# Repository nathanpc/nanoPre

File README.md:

# nanoPre

A simple, battery powered, HiFi preamp.

## Schematics

This is the pre-amplifier. As you can see it's extremely simple and it's designed to be able to fit in any enclosure (but it was designed to fit inside [this one](http://www.aliexpress.com/item/Aluminum-Project-Box-Enclousure-Case-Electronic-DIY-Power-amplifier-aluminum-shell-PCB-shell-power-instrument-shell/1799375798.html)).

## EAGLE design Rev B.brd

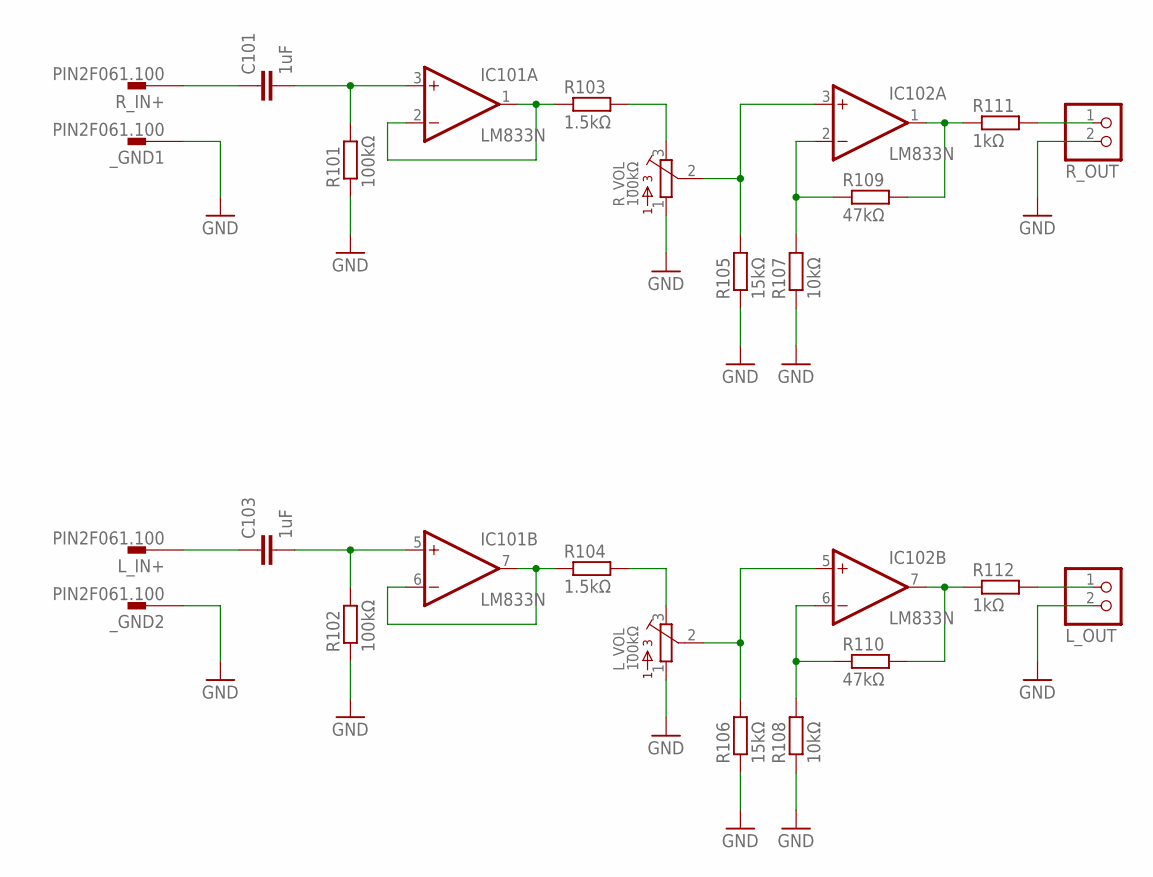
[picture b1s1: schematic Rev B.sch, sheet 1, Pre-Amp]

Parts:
C101, C103: 1uF; C150-072X183
IC101, IC102: LM833N; DIL08
L_IN+: PIN2F061.100; F061.100
L_OUT: JST_2PIN-THM; JST-PH-2-THM
L_VOL: 100kΩ; 3362U
R101, R102: 100kΩ; 0207/10
R103, R104: 1.5kΩ; 0207/10
R105, R106: 15kΩ; 0207/10
R107, R108: 10kΩ; 0207/10
R109, R110: 47kΩ; 0207/10
R111, R112: 1kΩ; 0207/10
R_IN+: PIN2F061.100; F061.100
R_OUT: JST_2PIN-THM; JST-PH-2-THM
R_VOL: 100kΩ; 3362U
_GND1, _GND2: PIN2F061.100; F061.100

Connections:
GND: L_OUT.2 (1), L_VOL.1, R101.1, R102.1, R105.1, R106.1, R107.1, R108.1, R_OUT.2 (1), R_VOL.1, _GND1.A1, _GND1.A2, _GND2.A1, _GND2.A2; also elsewhere on the board
unnamed: L_OUT.1 (2), R112.2
unnamed: R111.2, R_OUT.1 (2)
unnamed: C101.2, IC101.3 (+IN), R101.2
unnamed: C103.2, IC101.5 (+IN), R102.2
unnamed: C101.1, R_IN+.A1, R_IN+.A2
unnamed: C103.1, L_IN+.A1, L_IN+.A2
unnamed: IC101.1 (OUT), IC101.2 (-IN), R103.1
unnamed: IC102.3 (+IN), R105.2, R_VOL.2
unnamed: R103.2, R_VOL.3
unnamed: IC102.2 (-IN), R107.2, R109.1
unnamed: IC102.1 (OUT), R109.2, R111.1
unnamed: IC101.6 (-IN), IC101.7 (OUT), R104.1
unnamed: IC102.5 (+IN), L_VOL.2, R106.2
unnamed: L_VOL.3, R104.2
unnamed: IC102.6 (-IN), R108.2, R110.1
unnamed: IC102.7 (OUT), R110.2, R112.1

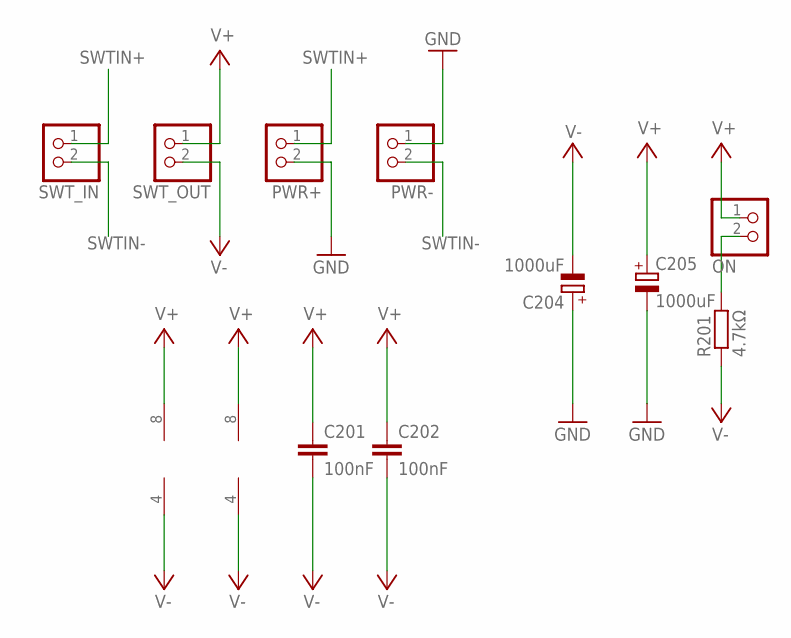
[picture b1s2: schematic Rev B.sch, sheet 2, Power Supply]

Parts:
C201, C202: 100nF; C025-025X050
C204, C205: 1000uF; E5-10,5
IC101, IC102: LM833N; DIL08
ON: JST_2PIN-THM; JST-PH-2-THM
PWR+: JST_2PIN-THM; JST-PH-2-THM
PWR-: JST_2PIN-THM; JST-PH-2-THM
R201: 4.7kΩ; 0207/10
SWT_IN: JST_2PIN-THM; JST-PH-2-THM
SWT_OUT: JST_2PIN-THM; JST-PH-2-THM

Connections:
GND: C204.+, C205.-, PWR+.2 (1), PWR-.1 (2); also elsewhere on the board
unnamed: ON.2 (1), R201.2
SWTIN+: PWR+.1 (2), SWT_IN.1 (2)
SWTIN-: PWR-.2 (1), SWT_IN.2 (1)
V+: C201.1, C202.1, C205.+, IC101.8 (V+), IC102.8 (V+), ON.1 (2), SWT_OUT.1 (2)
V-: C201.2, C202.2, C204.-, IC101.4 (V-), IC102.4 (V-), R201.1, SWT_OUT.2 (1)

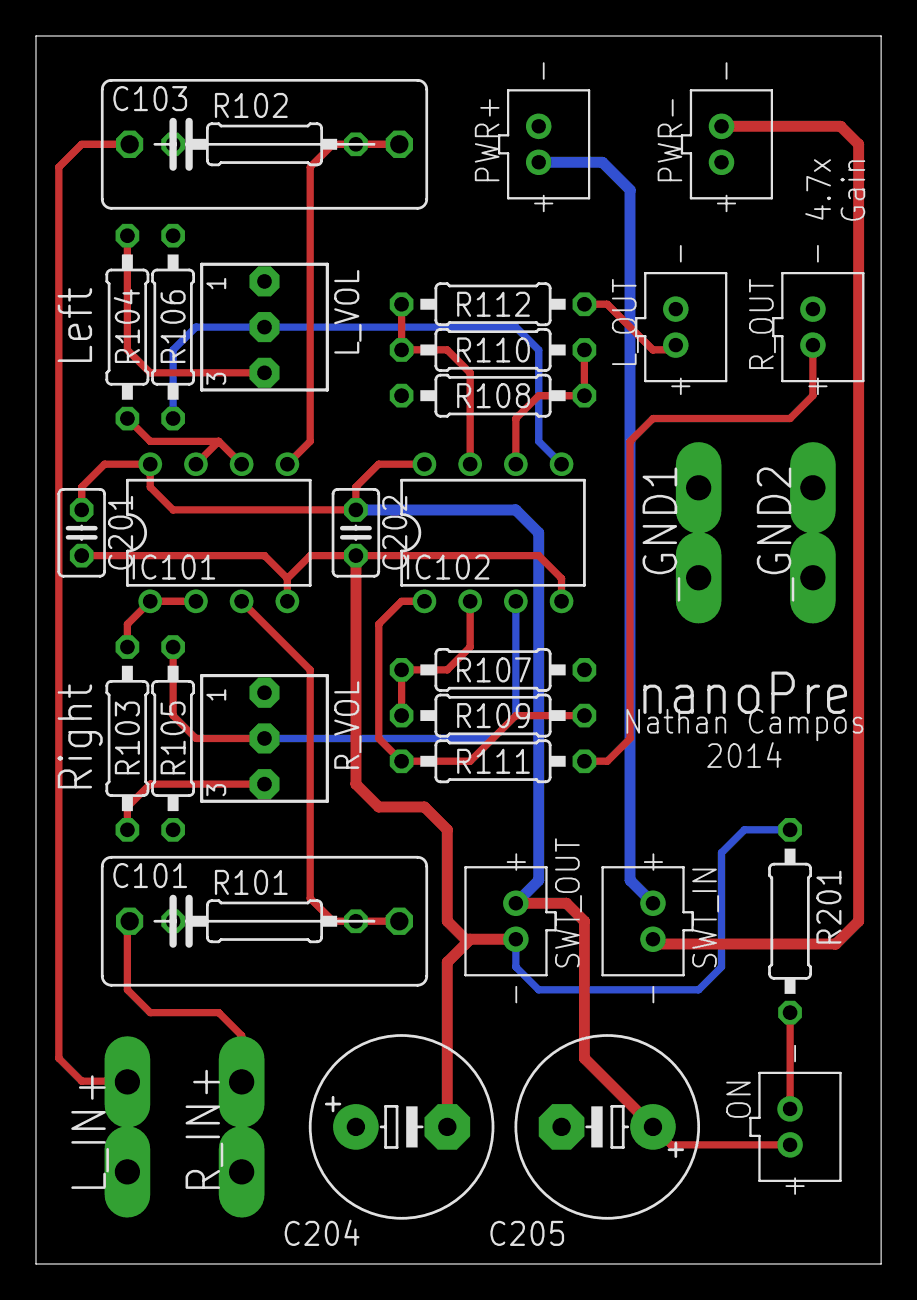
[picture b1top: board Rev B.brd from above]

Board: 2 copper layers, 47.0 x 68.2 mm, 34 parts (0 on the bottom side), 22 nets.

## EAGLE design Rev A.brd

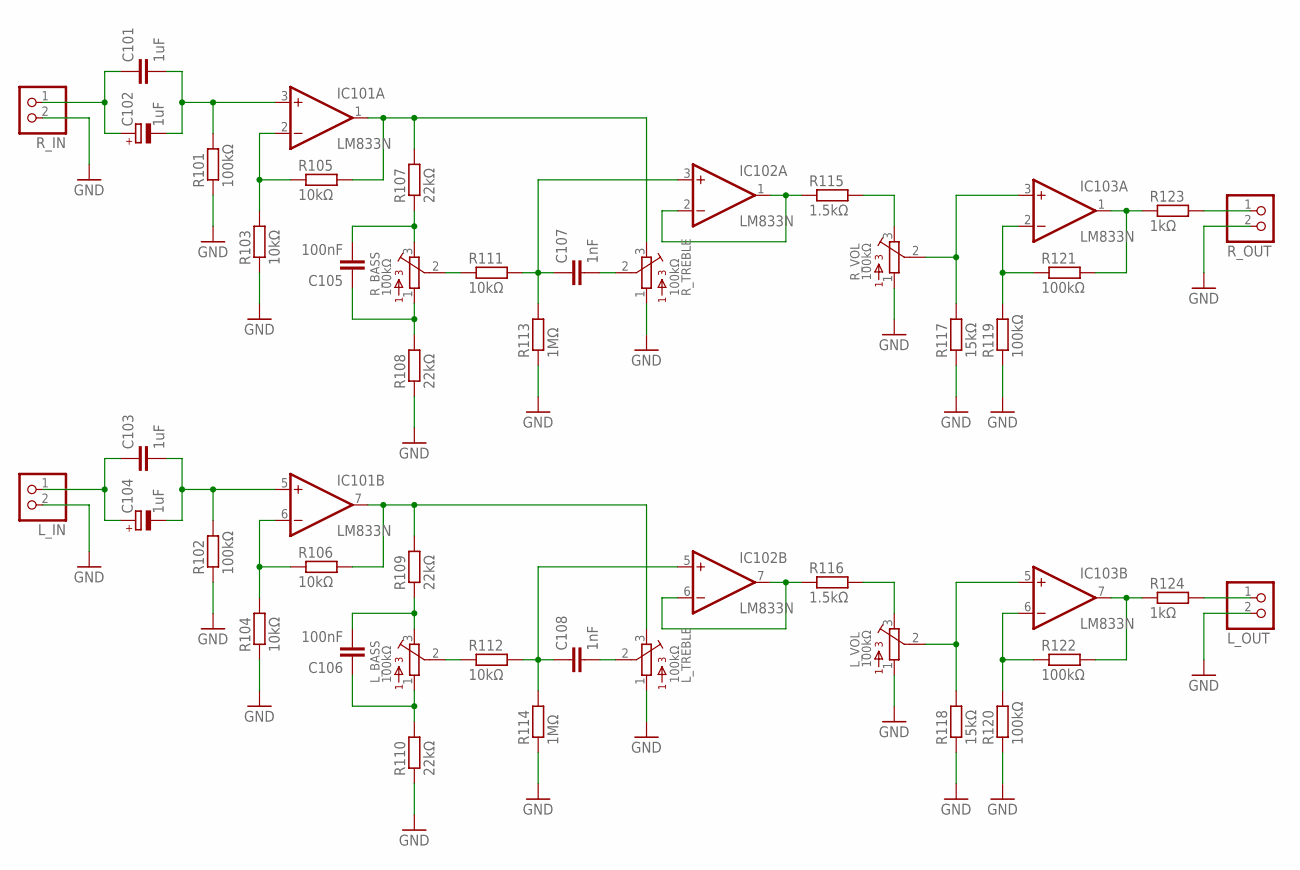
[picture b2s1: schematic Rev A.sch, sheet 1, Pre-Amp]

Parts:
C101, C103: 1uF; C150-072X183
C102, C104: 1uF; E2-5
C105, C106: 100nF; C050-025X075
C107, C108: 1nF; C050-025X075
IC101, IC102, IC103: LM833N; DIL08
L_BASS: 100kΩ; 3362U
L_IN: JST_2PIN-THM; JST-PH-2-THM
L_OUT: JST_2PIN-THM; JST-PH-2-THM
L_TREBLE: 100kΩ; 3362U
L_VOL: 100kΩ; 3362U
R101, R102, R119, R120, R121, R122: 100kΩ; 0207/10
R103, R104, R105, R106, R111, R112: 10kΩ; 0207/10
R107, R108, R109, R110: 22kΩ; 0207/10
R113, R114: 1MΩ; 0207/10
R115, R116: 1.5kΩ; 0207/10
R117, R118: 15kΩ; 0207/10
R123, R124: 1kΩ; 0207/10
R_BASS: 100kΩ; 3362U
R_IN: JST_2PIN-THM; JST-PH-2-THM
R_OUT: JST_2PIN-THM; JST-PH-2-THM
R_TREBLE: 100kΩ; 3362U
R_VOL: 100kΩ; 3362U

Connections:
GND: L_IN.2 (1), L_OUT.2 (1), L_TREBLE.1, L_VOL.1, R101.1, R102.1, R103.1, R104.1, R108.1, R110.1, R113.1, R114.1, R117.1, R118.1, R119.1, R120.1, R_IN.2 (1), R_OUT.2 (1), R_TREBLE.1, R_VOL.1; also elsewhere on the board
unnamed: L_OUT.1 (2), R124.2
unnamed: R123.2, R_OUT.1 (2)
unnamed: C101.2, C102.-, IC101.3 (+IN), R101.2
unnamed: C103.2, C104.-, IC101.5 (+IN), R102.2
unnamed: C101.1, C102.+, R_IN.1 (2)
unnamed: C103.1, C104.+, L_IN.1 (2)
unnamed: IC102.1 (OUT), IC102.2 (-IN), R115.1
unnamed: C105.2, R107.1, R_BASS.3
unnamed: IC103.3 (+IN), R117.2, R_VOL.2
unnamed: IC101.2 (-IN), R103.2, R105.1
unnamed: R115.2, R_VOL.3
unnamed: C105.1, R108.2, R_BASS.1
unnamed: IC103.2 (-IN), R119.2, R121.1
unnamed: IC103.1 (OUT), R121.2, R123.1
unnamed: R111.1, R_BASS.2
unnamed: C107.1, IC102.3 (+IN), R111.2, R113.2
unnamed: C107.2, R_TREBLE.2
unnamed: IC102.6 (-IN), IC102.7 (OUT), R116.1
unnamed: IC101.6 (-IN), R104.2, R106.1
unnamed: IC101.1 (OUT), R105.2, R107.2, R_TREBLE.3
unnamed: IC103.5 (+IN), L_VOL.2, R118.2
unnamed: L_VOL.3, R116.2
unnamed: C106.2, L_BASS.3, R109.1
unnamed: C106.1, L_BASS.1, R110.2
unnamed: L_BASS.2, R112.1
unnamed: C108.1, IC102.5 (+IN), R112.2, R114.2
unnamed: C108.2, L_TREBLE.2
unnamed: IC101.7 (OUT), L_TREBLE.3, R106.2, R109.2
unnamed: IC103.6 (-IN), R120.2, R122.1
unnamed: IC103.7 (OUT), R122.2, R124.1

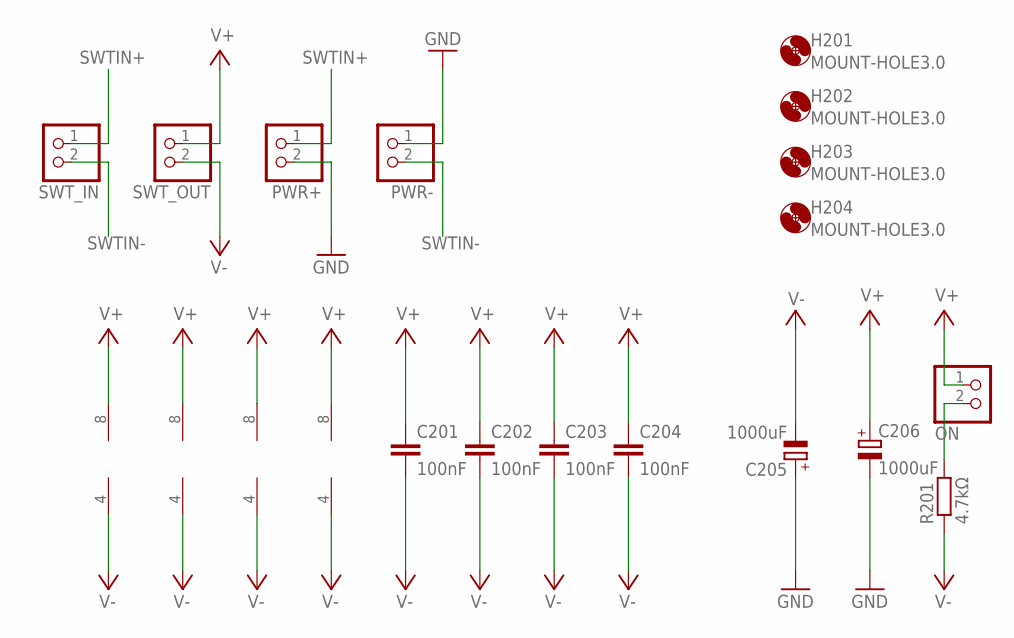
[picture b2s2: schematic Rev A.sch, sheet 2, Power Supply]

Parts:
C201, C202, C203, C204: 100nF; C025-025X050
C205, C206: 1000uF; E5-10,5
H201, H202, H203, H204: MOUNT-HOLE3.0; 3,0
IC101, IC102, IC103: LM833N; DIL08
IC201: LM393N; DIL08
ON: JST_2PIN-THM; JST-PH-2-THM
PWR+: JST_2PIN-THM; JST-PH-2-THM
PWR-: JST_2PIN-THM; JST-PH-2-THM
R201: 4.7kΩ; 0207/10
SWT_IN: JST_2PIN-THM; JST-PH-2-THM
SWT_OUT: JST_2PIN-THM; JST-PH-2-THM

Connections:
GND: C205.+, C206.-, PWR+.2 (1), PWR-.1 (2); also elsewhere on the board
unnamed: ON.2 (1), R201.2
SWTIN+: PWR+.1 (2), SWT_IN.1 (2)
SWTIN-: PWR-.2 (1), SWT_IN.2 (1)
V+: C201.1, C202.1, C203.1, C204.1, C206.+, IC101.8 (V+), IC102.8 (V+), IC103.8 (V+), IC201.8 (V+), ON.1 (2), SWT_OUT.1 (2); also elsewhere on the board
V-: C201.2, C202.2, C203.2, C204.2, C205.-, IC101.4 (V-), IC102.4 (V-), IC103.4 (V-), IC201.4 (V-), R201.1, SWT_OUT.2 (1); also elsewhere on the board

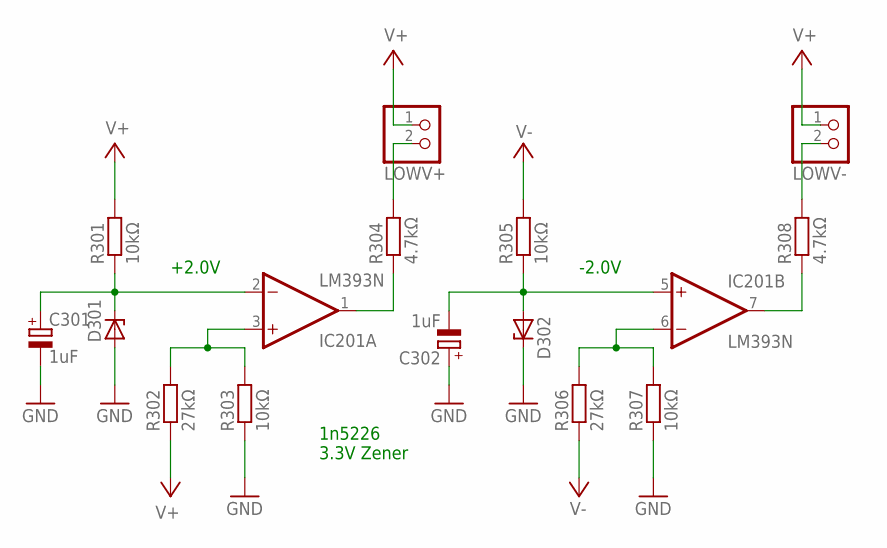
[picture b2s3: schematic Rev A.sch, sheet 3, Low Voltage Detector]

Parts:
C301, C302: 1uF; E2-5
D301, D302: BZV10; DO34Z7
IC201: LM393N; DIL08
LOWV+: JST_2PIN-THM; JST-PH-2-THM
LOWV-: JST_2PIN-THM; JST-PH-2-THM
R301, R303, R305, R307: 10kΩ; 0207/10
R302, R306: 27kΩ; 0207/10
R304, R308: 4.7kΩ; 0207/10

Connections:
GND: C301.-, C302.+, D301.A, D302.C, R303.1, R307.1; also elsewhere on the board
unnamed: C301.+, D301.C, IC201.2 (-IN), R301.1
unnamed: C302.-, D302.A, IC201.5 (+IN), R305.1
unnamed: LOWV+.2 (1), R304.2
unnamed: IC201.3 (+IN), R302.2, R303.2
unnamed: IC201.6 (-IN), R306.2, R307.2
unnamed: IC201.1 (OUT), R304.1
unnamed: LOWV-.2 (1), R308.2
unnamed: IC201.7 (OUT), R308.1
V+: LOWV+.1 (2), LOWV-.1 (2), R301.2, R302.1; also elsewhere on the board
V-: R305.2, R306.1; also elsewhere on the board

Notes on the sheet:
1n5226 3.3V Zener
+2.0V
-2.0V

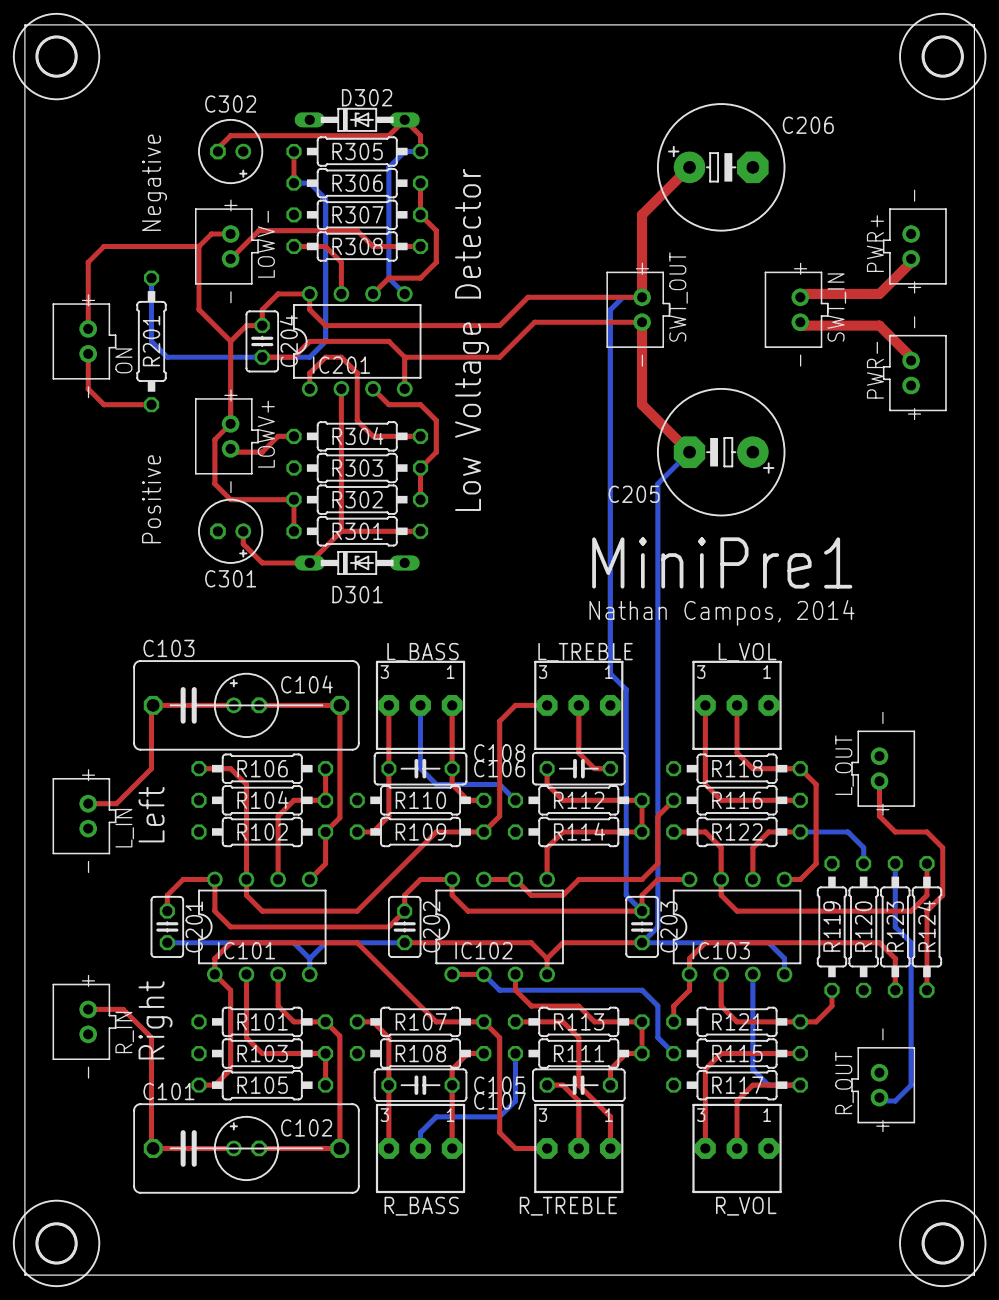
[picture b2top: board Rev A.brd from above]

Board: 4 copper layers, 76.2 x 100.3 mm, 76 parts (0 on the bottom side), 44 nets.

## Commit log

2014-08-22 Finished schematic and PCB layout
2014-08-22 Exported the schematic
2014-08-22 Ready for production
2014-08-22 Updated the README
2014-09-15 Rev B
2014-09-15 Updated the README with Rev B and changed the name of the project
2014-09-15 Rev B ready for production
